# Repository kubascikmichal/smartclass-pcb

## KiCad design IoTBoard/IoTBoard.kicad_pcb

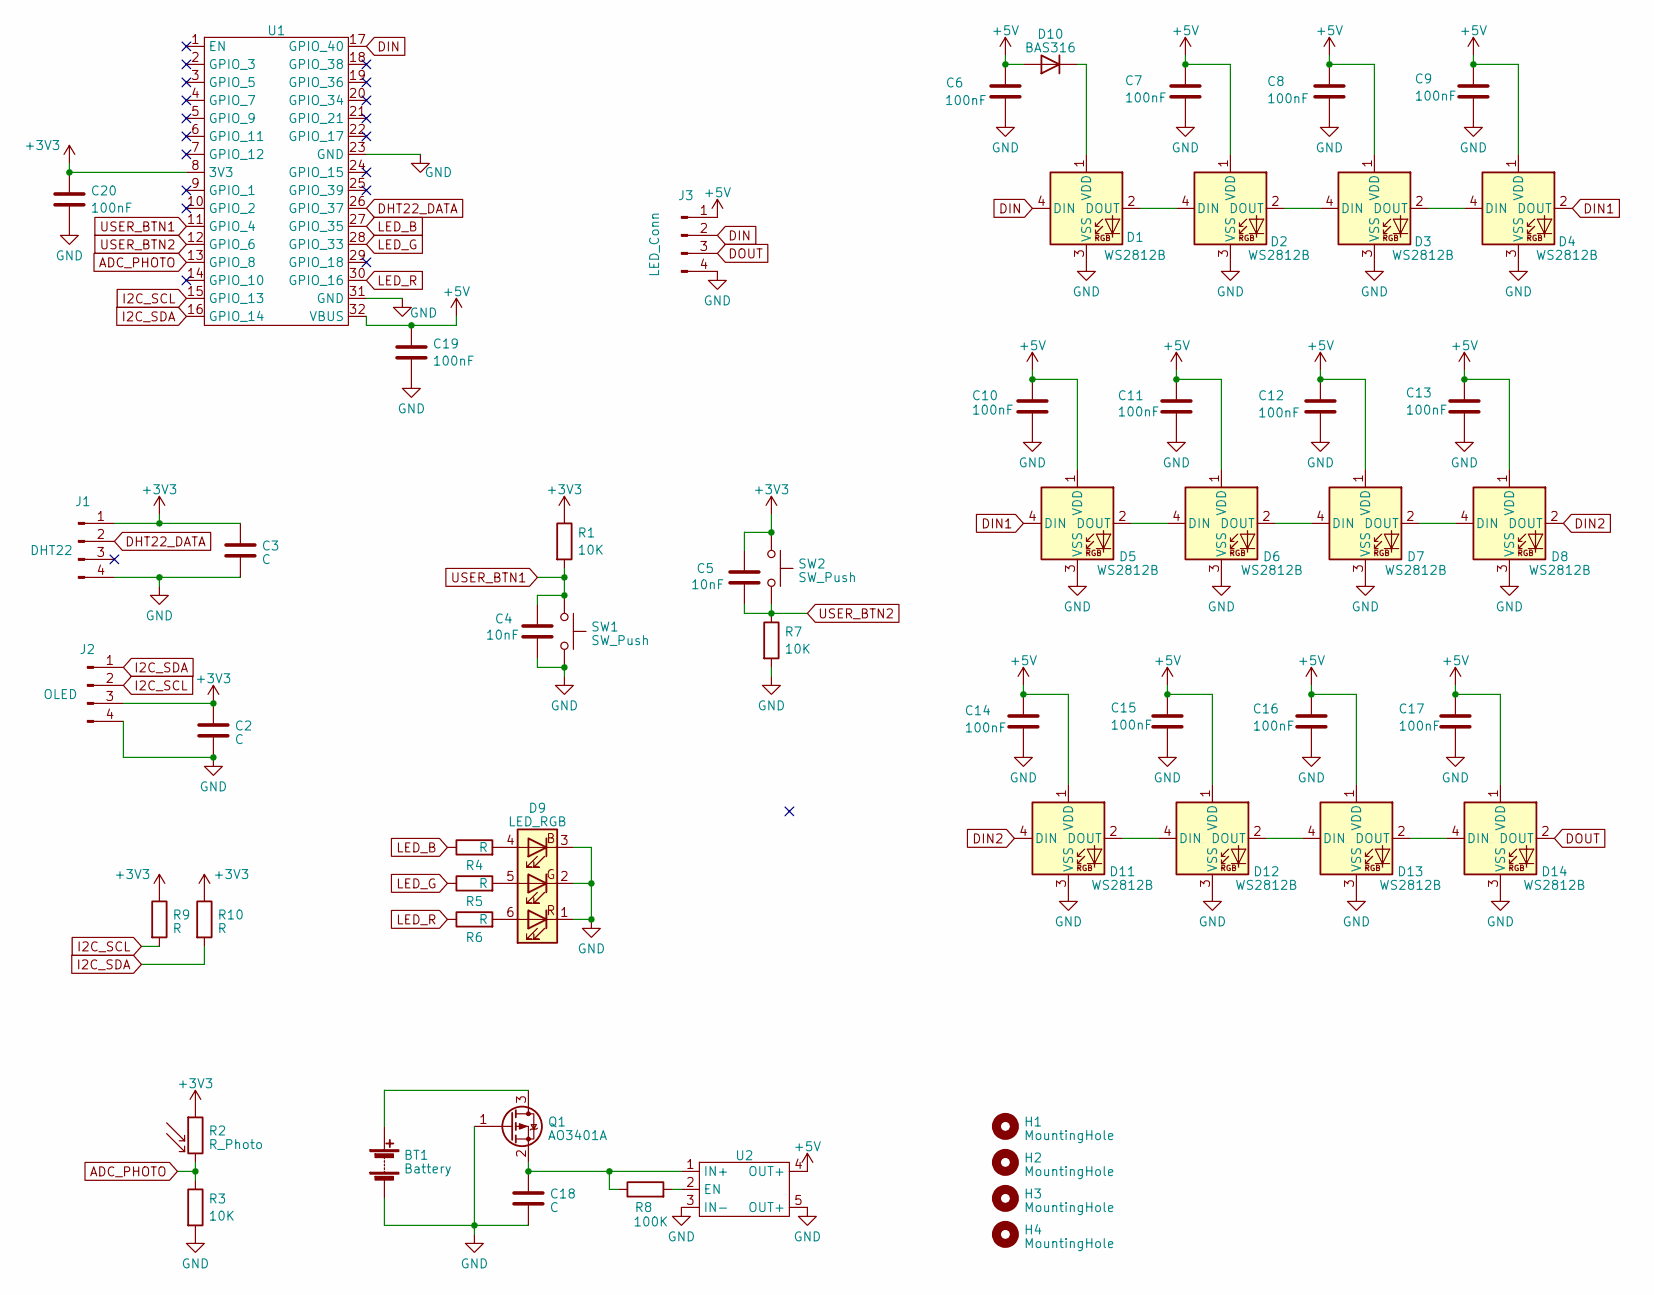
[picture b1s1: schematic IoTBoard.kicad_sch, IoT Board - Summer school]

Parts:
BT1: Battery; BatteryHolder_Keystone_2479_3xAAA
C2, C3, C18: C; C_0805_2012Metric
C4, C5: 10nF; C_0805_2012Metric
C6, C7, C8, C9, C10, C11, C12, C13, C14, C15, C16, C17, C19, C20: 100nF; C_0805_2012Metric
D1, D2, D3, D4, D5, D6, D7, D8, D11, D12, D13, D14: WS2812B; LED_WS2812B_PLCC4_5.0x5.0mm_P3.2mm
D9: LED_RGB; LED_WS2812_PLCC6_5.0x5.0mm_P1.6mm
D10: BAS316; D_SOD-323_HandSoldering
H1, H2, H3, H4: MountingHole; MountingHole_2.2mm_M2
J1: DHT22; PinHeader_1x04_P2.54mm_Vertical
J2: OLED; PinHeader_1x04_P2.54mm_Vertical
J3: LED_Conn; PinHeader_1x04_P2.54mm_Vertical
Q1: AO3401A; SOT-23
R1, R3, R7: 10K; R_0805_2012Metric
R2: R_Photo; R_LDR_4.9x4.2mm_P2.54mm_Vertical
R4, R5, R6, R9, R10: R; R_0805_2012Metric
R8: 100K; R_0805_2012Metric
SW1, SW2: SW_Push; SW_SPST_Omron_B3FS-105xP
U1: WEMOS_S2_mini_traced
U2: BuckBoost5V

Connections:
+3V3: C2.1, C3.1, C5.1, C20.1, J1.1, J2.3, R1.1, R2.1, R9.1, R10.1, SW2.1, U1.8 (3V3)
+5V: C6.1, C7.1, C8.1, C9.1, C10.1, C11.1, C12.1, C13.1, C14.1, C15.1, C16.1, C17.1, C19.1, D2.1 (VDD), D3.1 (VDD), D4.1 (VDD), D5.1 (VDD), D6.1 (VDD), D7.1 (VDD), D8.1 (VDD), D10.2 (A), D11.1 (VDD), D12.1 (VDD), D13.1 (VDD), D14.1 (VDD), J3.1, U1.32 (VBUS), U2.4 (OUT+)
ADC_PHOTO: R2.2, R3.1, U1.13 (GPIO_8)
DHT22_DATA: J1.2, U1.26 (GPIO_37)
DIN: D1.4 (DIN), J3.2, U1.17 (GPIO_40)
DIN1: D4.2 (DOUT), D5.4 (DIN)
DIN2: D8.2 (DOUT), D11.4 (DIN)
DOUT: D14.2 (DOUT), J3.3
GND: BT1.2 (-), C2.2, C3.2, C4.2, C6.2, C7.2, C8.2, C9.2, C10.2, C11.2, C12.2, C13.2, C14.2, C15.2, C16.2, C17.2, C18.2, C19.2, C20.2, D1.3 (VSS), D2.3 (VSS), D3.3 (VSS), D4.3 (VSS), D5.3 (VSS), D6.3 (VSS), D7.3 (VSS), D8.3 (VSS), D9.1 (RK), D9.2 (GK), D9.3 (BK), D11.3 (VSS), D12.3 (VSS), D13.3 (VSS), D14.3 (VSS), J1.4, J2.4, J3.4, Q1.1 (G), R3.2, R7.2, SW1.2, U1.23 (GND), U1.31 (GND), U2.3 (IN-), U2.5 (OUT+)
I2C_SCL: J2.2, R9.2, U1.15 (GPIO_13)
I2C_SDA: J2.1, R10.2, U1.16 (GPIO_14)
LED_B: R4.1, U1.27 (GPIO_35)
LED_G: R5.1, U1.28 (GPIO_33)
LED_R: R6.1, U1.30 (GPIO_16)
unnamed: BT1.1 (+), Q1.3 (D)
unnamed: D1.2 (DOUT), D2.4 (DIN)
unnamed: D1.1 (VDD), D10.1 (K)
unnamed: D2.2 (DOUT), D3.4 (DIN)
unnamed: D3.2 (DOUT), D4.4 (DIN)
unnamed: D5.2 (DOUT), D6.4 (DIN)
unnamed: D6.2 (DOUT), D7.4 (DIN)
unnamed: D7.2 (DOUT), D8.4 (DIN)
unnamed: D9.4 (BA), R4.2
unnamed: D9.5 (GA), R5.2
unnamed: D9.6 (RA), R6.2
unnamed: D11.2 (DOUT), D12.4 (DIN)
unnamed: D12.2 (DOUT), D13.4 (DIN)
unnamed: D13.2 (DOUT), D14.4 (DIN)
unnamed: C18.1, Q1.2 (S), R8.1, U2.1 (IN+)
unnamed: R8.2, U2.2 (EN)
USER_BTN1: C4.1, R1.2, SW1.1, U1.11 (GPIO_4)
USER_BTN2: C5.2, R7.1, SW2.2, U1.12 (GPIO_6)

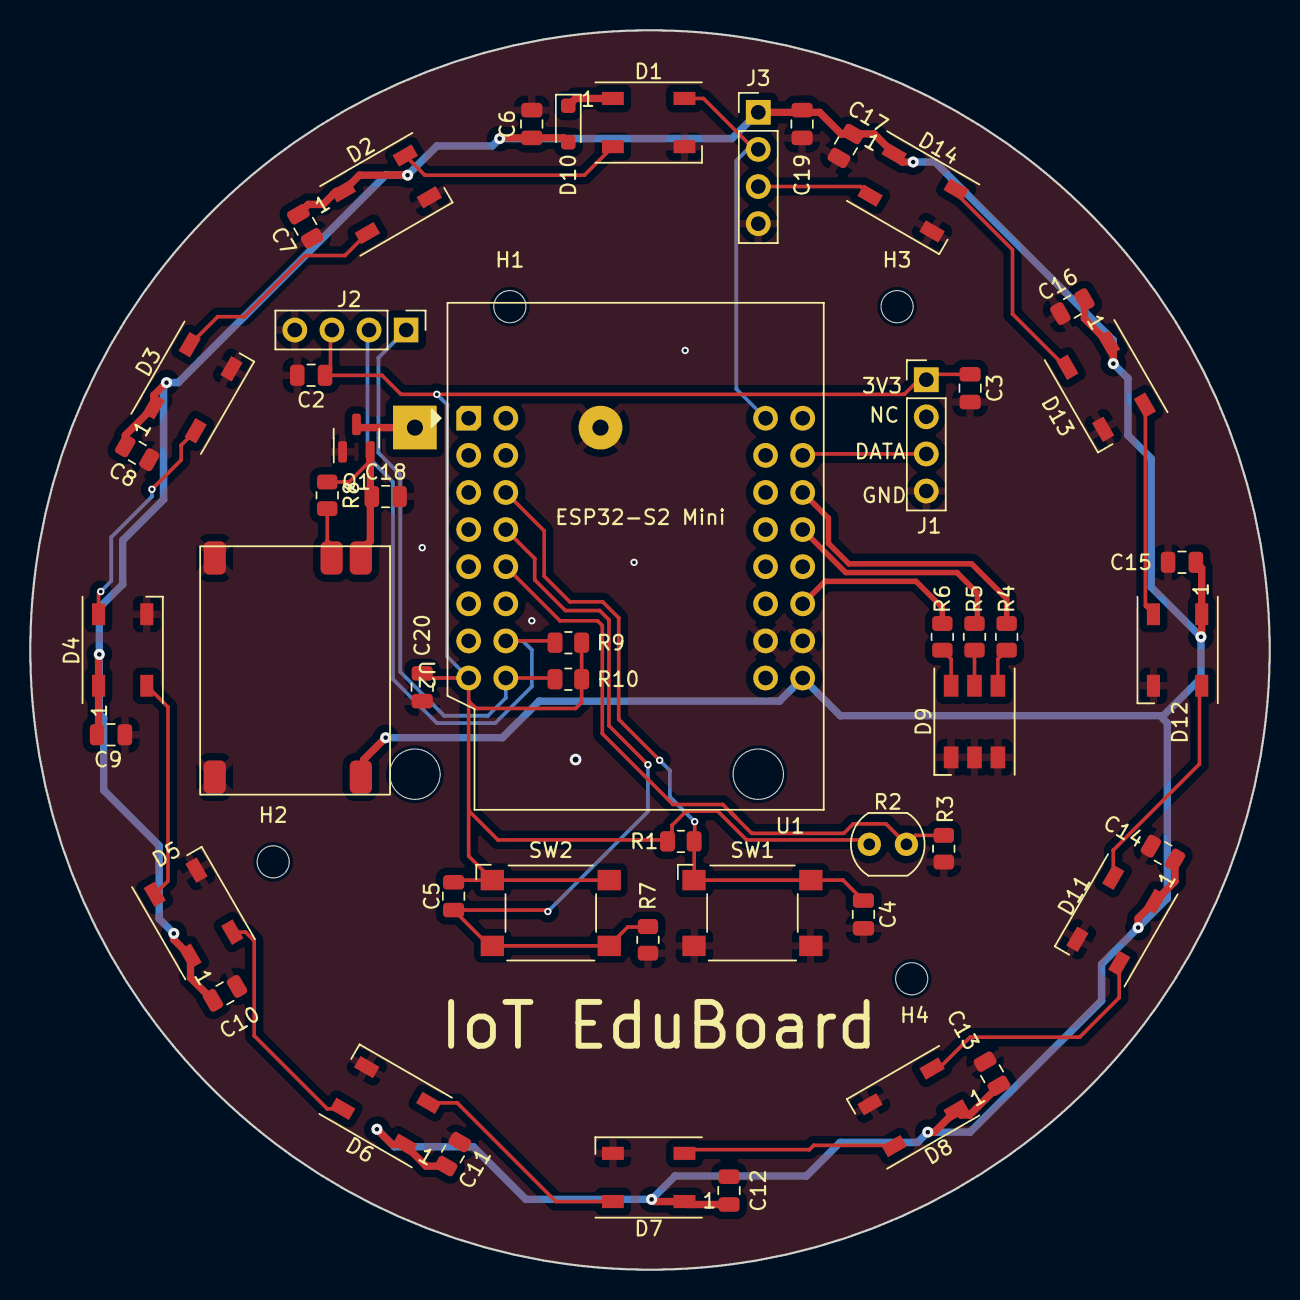
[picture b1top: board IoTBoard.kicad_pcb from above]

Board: 2 copper layers, 84.8 x 84.8 mm, 56 parts (1 on the bottom side), 32 nets.

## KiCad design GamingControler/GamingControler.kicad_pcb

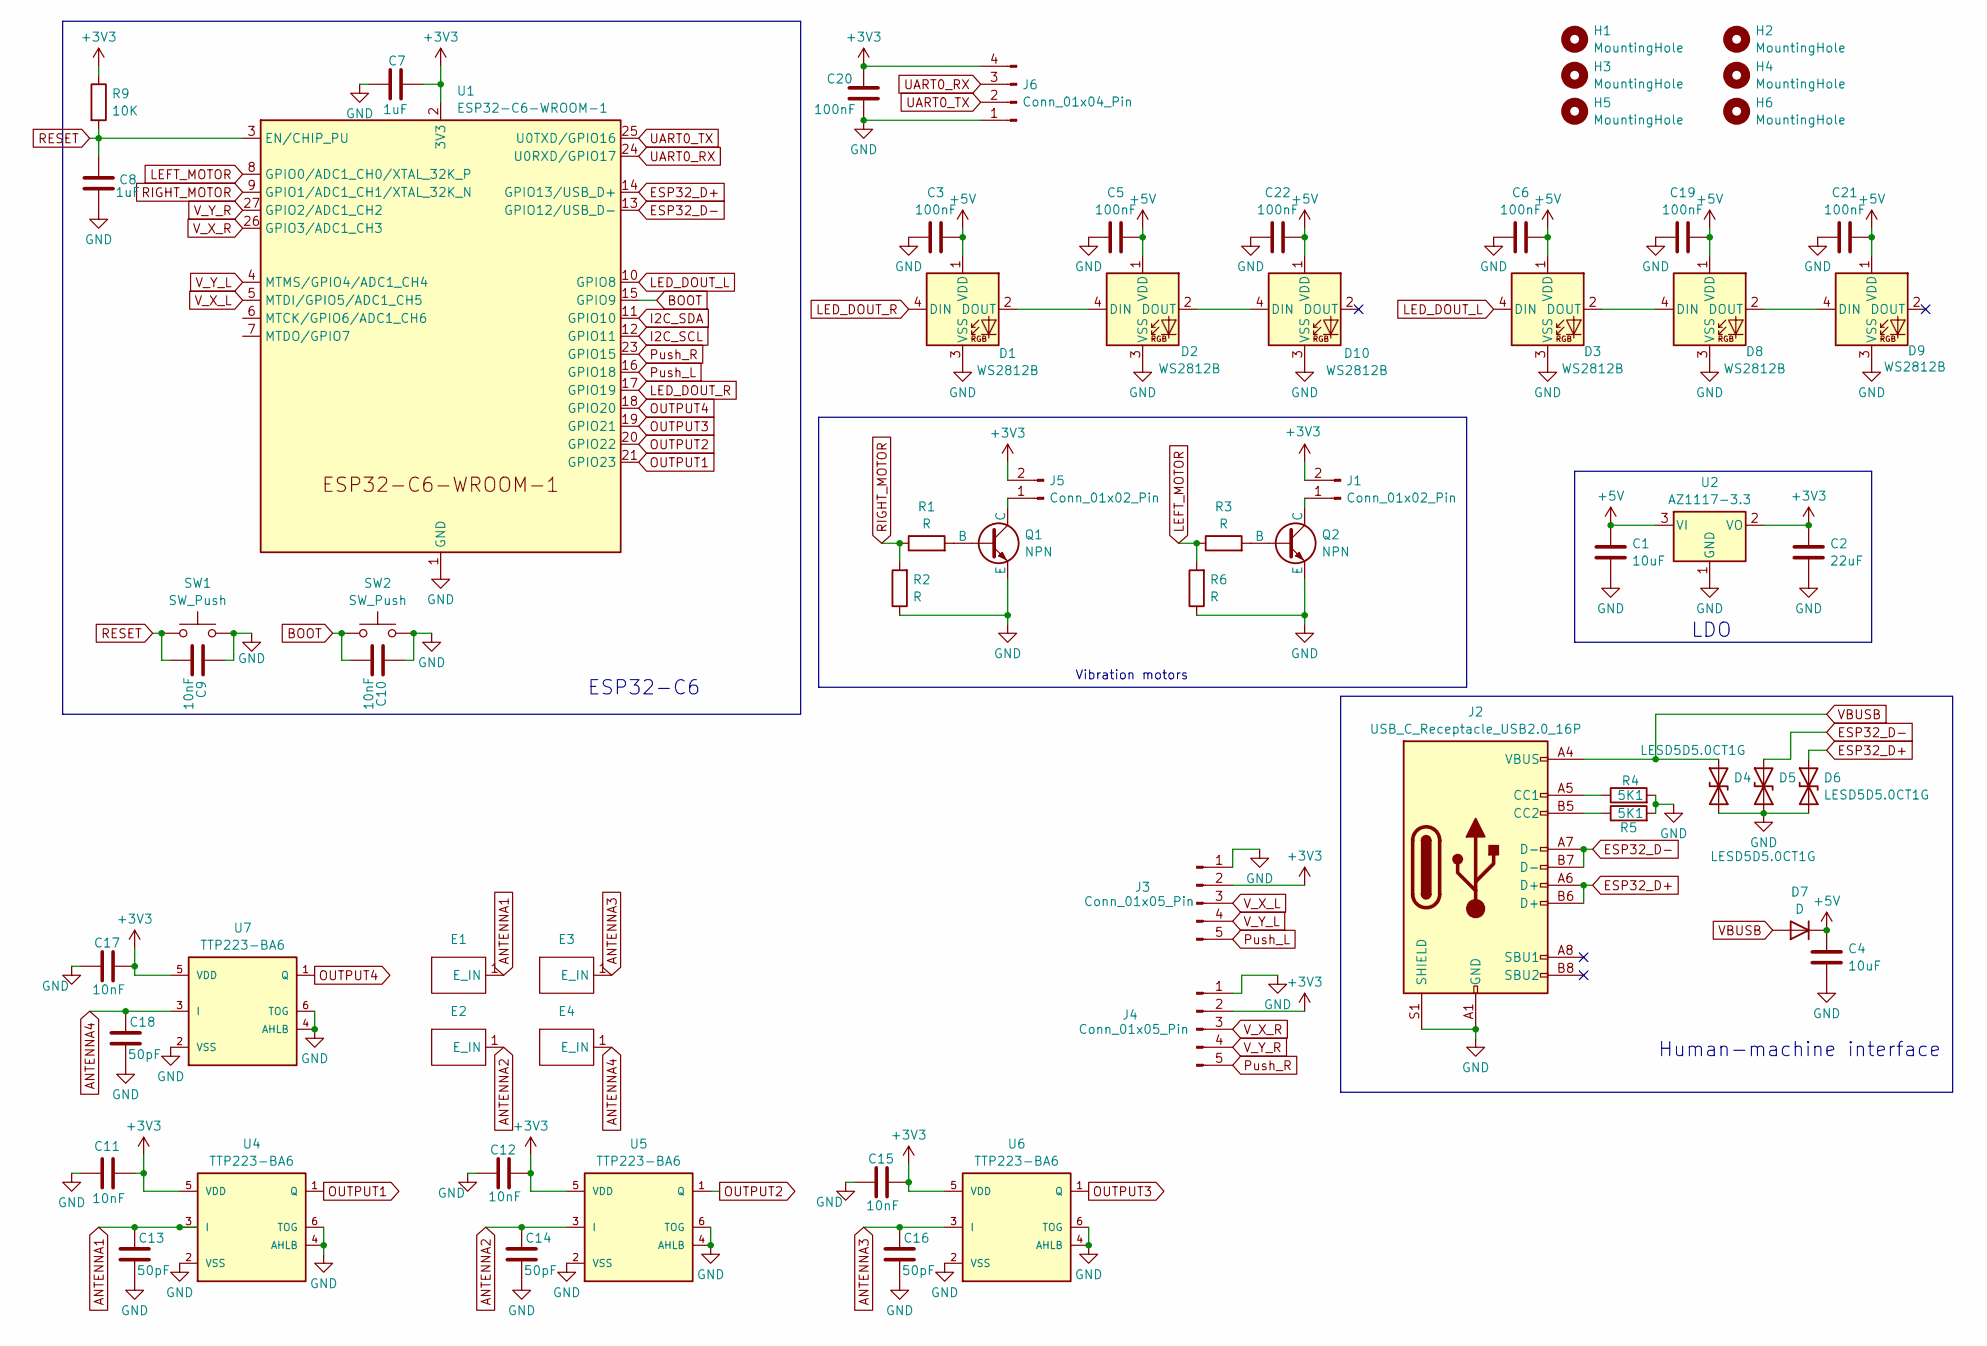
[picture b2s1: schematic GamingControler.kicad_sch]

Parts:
C1, C4: 10uF; C_0805_2012Metric
C2: 22uF; C_0805_2012Metric
C3, C5, C6, C19, C20, C21, C22: 100nF; C_0805_2012Metric
C7, C8: 1uF; C_0805_2012Metric
C9, C10, C11, C12, C15, C17: 10nF; C_0805_2012Metric
C13, C14, C16, C18: 50pF; C_0805_2012Metric
D1, D2, D3, D8, D9, D10: WS2812B; LED_WS2812B_PLCC4_5.0x5.0mm_P3.2mm
D4, D5, D6: LESD5D5.0CT1G; D_SOD-523
D7: D; D_0805_2012Metric
E1, E2, E3, E4: Electrode_10x10mm
H1, H2, H3, H4, H5, H6: MountingHole; MountingHole_3.2mm_M3
J1, J5: Conn_01x02_Pin; PinSocket_1x02_P2.00mm_Vertical
J2: USB_C_Receptacle_USB2.0_16P; USB_C_Receptacle_G-Switch_GT-USB-7010ASV
J3, J4: Conn_01x05_Pin; PinHeader_1x05_P2.54mm_Vertical
J6: Conn_01x04_Pin; PinSocket_1x04_P2.54mm_Vertical
Q1, Q2: NPN; SOT-23
R1, R2, R3, R6: R; R_0805_2012Metric
R4, R5: 5K1; R_0805_2012Metric
R9: 10K; R_0805_2012Metric
SW1, SW2: SW_Push; SW_Push_1P1T_NO_6x6mm_H9.5mm
U1: ESP32-C6-WROOM-1
U2: AZ1117-3.3; TO-252-2
U4, U5, U6, U7: TTP223-BA6; TSOT-23-6_HandSoldering

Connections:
+3V3: C2.1, C7.2, C11.1, C12.1, C15.1, C17.1, C20.2, J1.2, J3.2, J4.2, J5.2, J6.4, R9.1, U1.2 (3V3), U2.2 (VO), U4.5 (VDD), U5.5 (VDD), U6.5 (VDD), U7.5 (VDD)
+5V: C1.1, C3.2, C4.1, C5.2, C6.2, C19.2, C21.2, C22.2, D1.1 (VDD), D2.1 (VDD), D3.1 (VDD), D7.1 (K), D8.1 (VDD), D9.1 (VDD), D10.1 (VDD), U2.3 (VI)
ANTENNA1: C13.2, E1.1 (E_IN), U4.3 (I)
ANTENNA2: C14.2, E2.1 (E_IN), U5.3 (I)
ANTENNA3: C16.2, E3.1 (E_IN), U6.3 (I)
ANTENNA4: C18.2, E4.1 (E_IN), U7.3 (I)
BOOT: C10.2, SW2.1, U1.15 (GPIO9)
ESP32_D+: D6.2 (A2), J2.A6 (D+), J2.B6 (D+), U1.14 (GPIO13/USB_D+)
ESP32_D-: D5.2 (A2), J2.A7 (D-), J2.B7 (D-), U1.13 (GPIO12/USB_D-)
GND: C1.2, C2.2, C3.1, C4.2, C5.1, C6.1, C7.1, C8.2, C9.1, C10.1, C11.2, C12.2, C13.1, C14.1, C15.2, C16.1, C17.2, C18.1, C19.1, C20.1, C21.1, C22.1, D1.3 (VSS), D2.3 (VSS), D3.3 (VSS), D4.1 (A1), D5.1 (A1), D6.1 (A1), D8.3 (VSS), D9.3 (VSS), D10.3 (VSS), J2.A1 (GND), J2.A12 (GND), J2.B1 (GND), J2.B12 (GND), J2.S1 (SHIELD), J3.1, J4.1, J6.1, Q1.3 (E), Q2.3 (E), R2.1, R4.2, R5.2, R6.1, SW1.2, SW2.2, U1.1 (GND), U1.28 (GND), U1.29 (GND), U2.1 (GND), U4.2 (VSS), U4.4 (AHLB), U4.6 (TOG), U5.2 (VSS), U5.4 (AHLB), U5.6 (TOG), U6.2 (VSS), U6.4 (AHLB), U6.6 (TOG), U7.2 (VSS), U7.4 (AHLB), U7.6 (TOG)
I2C_SCL: U1.12 (GPIO11)
I2C_SDA: U1.11 (GPIO10)
LED_DOUT_L: D3.4 (DIN), U1.10 (GPIO8)
LED_DOUT_R: D1.4 (DIN), U1.17 (GPIO19)
LEFT_MOTOR: R3.1, R6.2, U1.8 (GPIO0/ADC1_CH0/XTAL_32K_P)
unnamed: D1.2 (DOUT), D2.4 (DIN)
unnamed: D3.2 (DOUT), D8.4 (DIN)
unnamed: D8.2 (DOUT), D9.4 (DIN)
unnamed: D2.2 (DOUT), D10.4 (DIN)
unnamed: J1.1, Q2.1 (C)
unnamed: J2.A5 (CC1), R4.1
unnamed: J2.B5 (CC2), R5.1
unnamed: J5.1, Q1.1 (C)
unnamed: Q1.2 (B), R1.2
unnamed: Q2.2 (B), R3.2
OUTPUT1: U1.21 (GPIO23), U4.1 (Q)
OUTPUT2: U1.20 (GPIO22), U5.1 (Q)
OUTPUT3: U1.19 (GPIO21), U6.1 (Q)
OUTPUT4: U1.18 (GPIO20), U7.1 (Q)
Push_L: J3.5, U1.16 (GPIO18)
Push_R: J4.5, U1.23 (GPIO15)
RESET: C8.1, C9.2, R9.2, SW1.1, U1.3 (EN/CHIP_PU)
RIGHT_MOTOR: R1.1, R2.2, U1.9 (GPIO1/ADC1_CH1/XTAL_32K_N)
UART0_RX: J6.3, U1.24 (U0RXD/GPIO17)
UART0_TX: J6.2, U1.25 (U0TXD/GPIO16)
VBUSB: D4.2 (A2), D7.2 (A), J2.A4 (VBUS), J2.A9 (VBUS), J2.B4 (VBUS), J2.B9 (VBUS)
V_X_L: J3.3, U1.5 (MTDI/GPIO5/ADC1_CH5)
V_X_R: J4.3, U1.26 (GPIO3/ADC1_CH3)
V_Y_L: J3.4, U1.4 (MTMS/GPIO4/ADC1_CH4)
V_Y_R: J4.4, U1.27 (GPIO2/ADC1_CH2)

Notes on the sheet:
ESP32-C6
LDO
Vibration motors
Human-machine interface

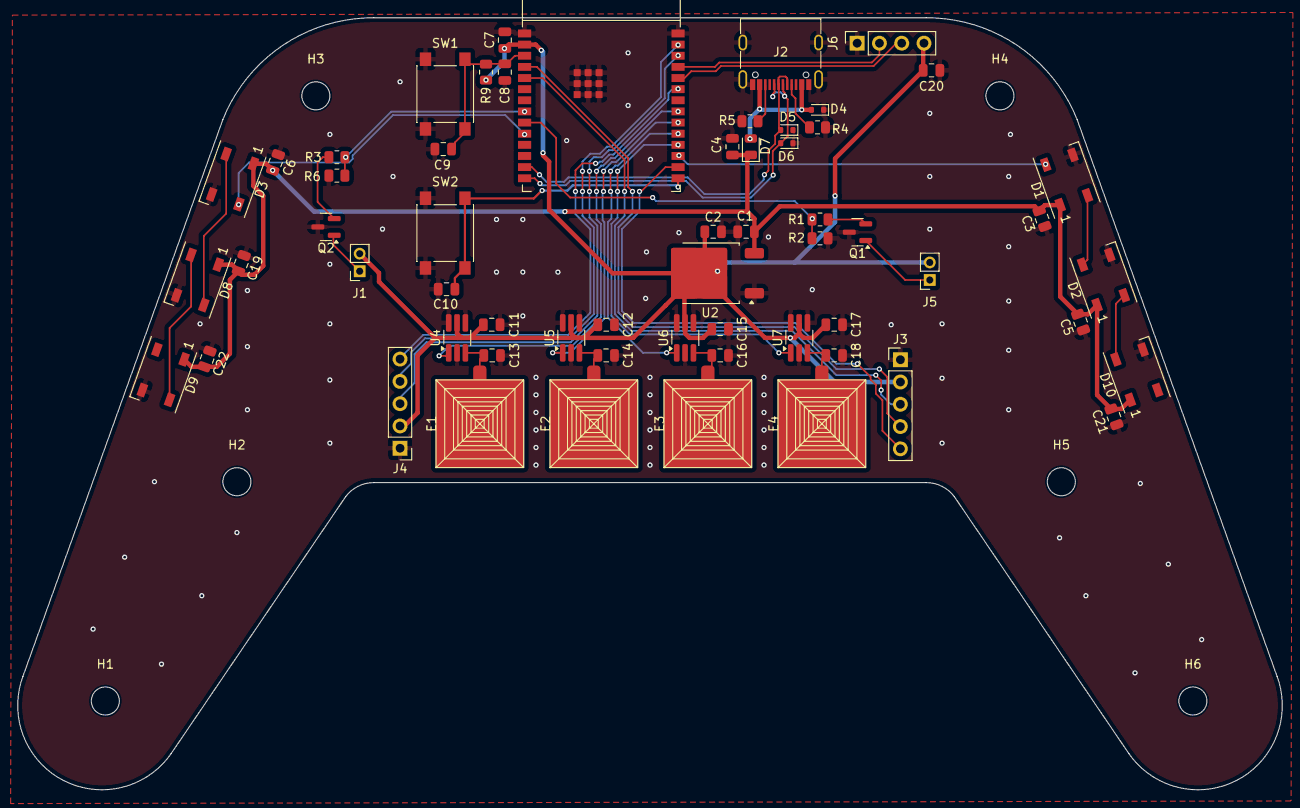
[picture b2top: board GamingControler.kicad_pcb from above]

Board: 2 copper layers, 144.2 x 88.0 mm, 65 parts (0 on the bottom side), 38 nets.

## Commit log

2024-07-18 init
2024-07-18 Summary
    Added USB-C flash and HMI interface
    Added ESP32-C6
    Added LDO
2024-07-18 Summary
    All around ESP32
2024-07-19 Replaced projects
    Deleted personal projects, and added just projects by name.
2024-07-19 Added multiple projects
    Added projects as business card, gaming controller, IoT board.
2024-07-24 GamingBoard
    Created prototype of PCB
2024-07-25 Final board
2024-07-25 summary
2024-08-01 Gaming controller
2024-08-02 IoT EduBoard
